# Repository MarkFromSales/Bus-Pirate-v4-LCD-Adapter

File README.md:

# Bus-Pirate-v4-LCD-Adapter
Remake of the Bus Pirate v4 LCD Adapter

Please refer to the amazing folks at Dangerous Prototypes for all the credit due!

http://dangerousprototypes.com/docs/Bus_Pirate

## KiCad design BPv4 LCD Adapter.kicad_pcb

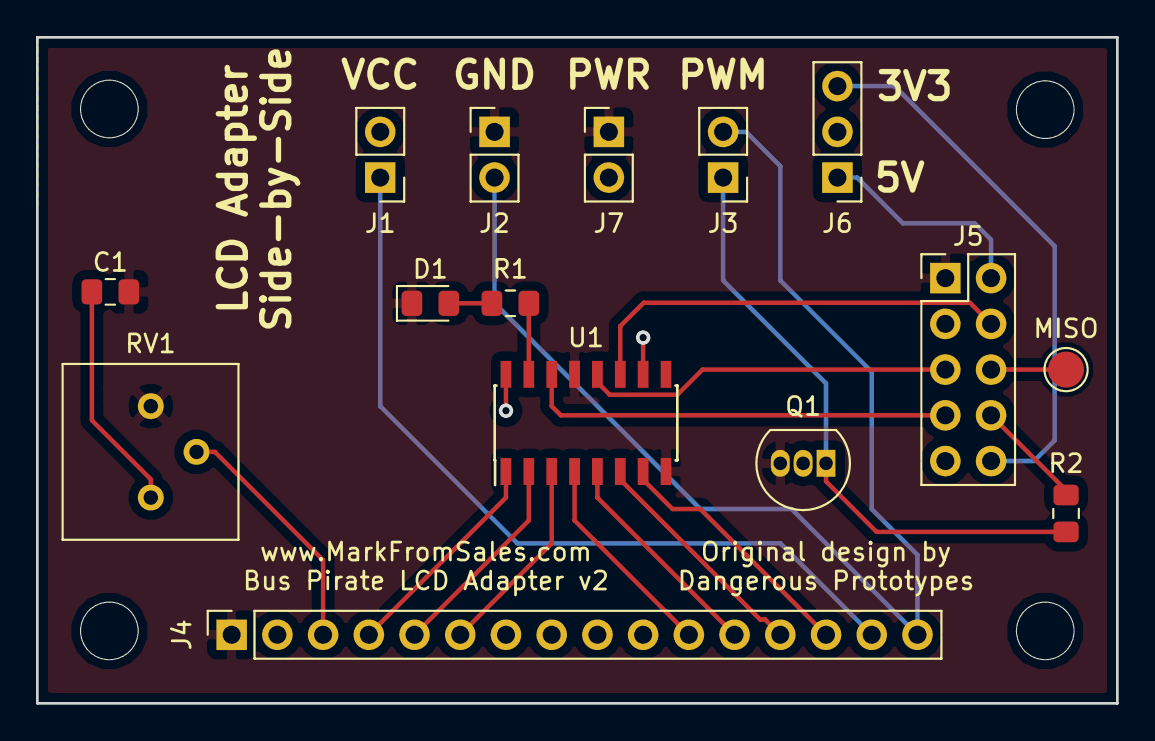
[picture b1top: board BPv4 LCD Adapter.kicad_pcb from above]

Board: 2 copper layers, 60.0 x 37.0 mm, 19 parts (0 on the bottom side), 23 nets.

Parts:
C1: C; C_0805_2012Metric_Pad1.15x1.40mm_HandSolder
D1: LED; LED_0805_2012Metric_Pad1.15x1.40mm_HandSolder
H1, H2, H3, H4: MountingHole; MountingHole_3.2mm_M3
J1: Jmp_Anode; PinHeader_1x02_P2.54mm_Vertical
J2: Jmp_Cathode; PinHeader_1x02_P2.54mm_Vertical
J3: Jmp_PWM; PinHeader_1x02_P2.54mm_Vertical
J4: Conn_LCD; PinSocket_1x16_P2.54mm_Vertical
J5: Conn_BusPirate; PinHeader_2x05_P2.54mm_Vertical
J6: Power_Select; PinHeader_1x03_P2.54mm_Vertical
J7: Conn_Pwr; PinHeader_1x02_P2.54mm_Vertical
Q1: BC337; TO-92_Inline
R1, R2: 1K; R_0805_2012Metric_Pad1.15x1.40mm_HandSolder
RV1: 10K; Potentiometer_Bourns_3386P_Vertical
TP1: TestPoint; TestPoint_Pad_D2.0mm
U1: 74HCT595; SOIC-16_3.9x9.9mm_P1.27mm

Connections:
/AUX: J5.8, R2.2
/CLK: J5.4, U1.11
/CS: J5.5, U1.12
/MISO: J5.6, TP1.1
/MOSI: J5.7, U1.14
/SWV33: J5.10, J6.3
/SWV50: J5.2, J6.1
GND: C1.2, D1.1, J2.1, J4.1, J5.1, J7.1, Q1.3, RV1.3, U1.8, U1.13
unnamed: D1.2, R1.2
unnamed: J1.1, J4.15
unnamed: J2.2, J3.2, J4.16
unnamed: J3.1, Q1.1
unnamed: J4.3, RV1.2
unnamed: J4.4, U1.1
unnamed: J4.5, U1.2
unnamed: J4.6, U1.3
unnamed: J4.11, U1.4
unnamed: J4.12, U1.5
unnamed: J4.13, U1.6
unnamed: J4.14, U1.7
unnamed: Q1.2, R2.1
unnamed: R1.1, U1.15
VCC: C1.1, J1.2, J6.2, J7.2, RV1.1, U1.10, U1.16

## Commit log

2019-02-02 Initial upload
2019-02-13 Updated structure
